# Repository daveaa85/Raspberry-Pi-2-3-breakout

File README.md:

This is an Eagle CAD project. It breaks out the 40 pin Raspberry Pi 2 and 3 io connector to a set of 3 rows of header pins.

It was created to make it easier to wire up and monitor pins. The way I use it is to populate the board with 2 rows of headers. The last set of holes are left open. That way DMM probes have a hole to drop into, and not slip off the target signal.

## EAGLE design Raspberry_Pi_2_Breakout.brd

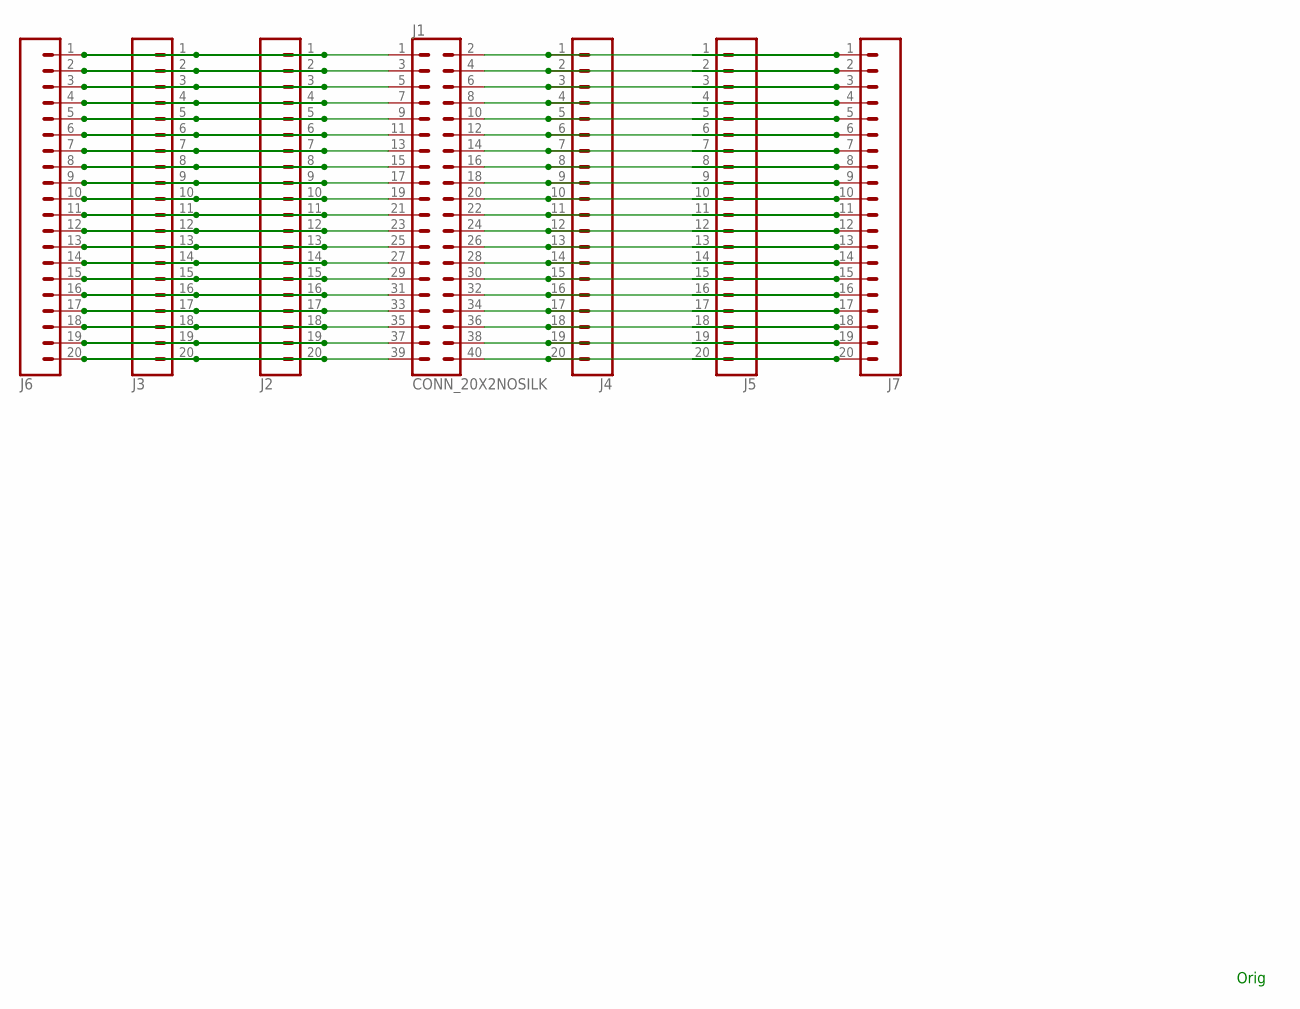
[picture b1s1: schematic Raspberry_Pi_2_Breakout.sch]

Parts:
J1: CONN_20X2NOSILK; 2X20_NOSILK
J2, J3, J4, J5, J6, J7: CONN_20NOSILK; 1X20_NOSILK

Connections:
unnamed: J1.1, J2.1, J3.1, J6.1
unnamed: J1.2, J4.1, J5.1, J7.1
unnamed: J1.4, J4.2, J5.2, J7.2
unnamed: J1.6, J4.3, J5.3, J7.3
unnamed: J1.8, J4.4, J5.4, J7.4
unnamed: J1.10, J4.5, J5.5, J7.5
unnamed: J1.12, J4.6, J5.6, J7.6
unnamed: J1.14, J4.7, J5.7, J7.7
unnamed: J1.16, J4.8, J5.8, J7.8
unnamed: J1.18, J4.9, J5.9, J7.9
unnamed: J1.20, J4.10, J5.10, J7.10
unnamed: J1.22, J4.11, J5.11, J7.11
unnamed: J1.24, J4.12, J5.12, J7.12
unnamed: J1.26, J4.13, J5.13, J7.13
unnamed: J1.28, J4.14, J5.14, J7.14
unnamed: J1.30, J4.15, J5.15, J7.15
unnamed: J1.32, J4.16, J5.16, J7.16
unnamed: J1.34, J4.17, J5.17, J7.17
unnamed: J1.36, J4.18, J5.18, J7.18
unnamed: J1.38, J4.19, J5.19, J7.19
unnamed: J1.40, J4.20, J5.20, J7.20
unnamed: J1.39, J2.20, J3.20, J6.20
unnamed: J1.37, J2.19, J3.19, J6.19
unnamed: J1.35, J2.18, J3.18, J6.18
unnamed: J1.33, J2.17, J3.17, J6.17
unnamed: J1.31, J2.16, J3.16, J6.16
unnamed: J1.29, J2.15, J3.15, J6.15
unnamed: J1.27, J2.14, J3.14, J6.14
unnamed: J1.25, J2.13, J3.13, J6.13
unnamed: J1.23, J2.12, J3.12, J6.12
unnamed: J1.21, J2.11, J3.11, J6.11
unnamed: J1.19, J2.10, J3.10, J6.10
unnamed: J1.17, J2.9, J3.9, J6.9
unnamed: J1.15, J2.8, J3.8, J6.8
unnamed: J1.13, J2.7, J3.7, J6.7
unnamed: J1.11, J2.6, J3.6, J6.6
unnamed: J1.9, J2.5, J3.5, J6.5
unnamed: J1.7, J2.4, J3.4, J6.4
unnamed: J1.5, J2.3, J3.3, J6.3
unnamed: J1.3, J2.2, J3.2, J6.2

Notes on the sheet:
Orig

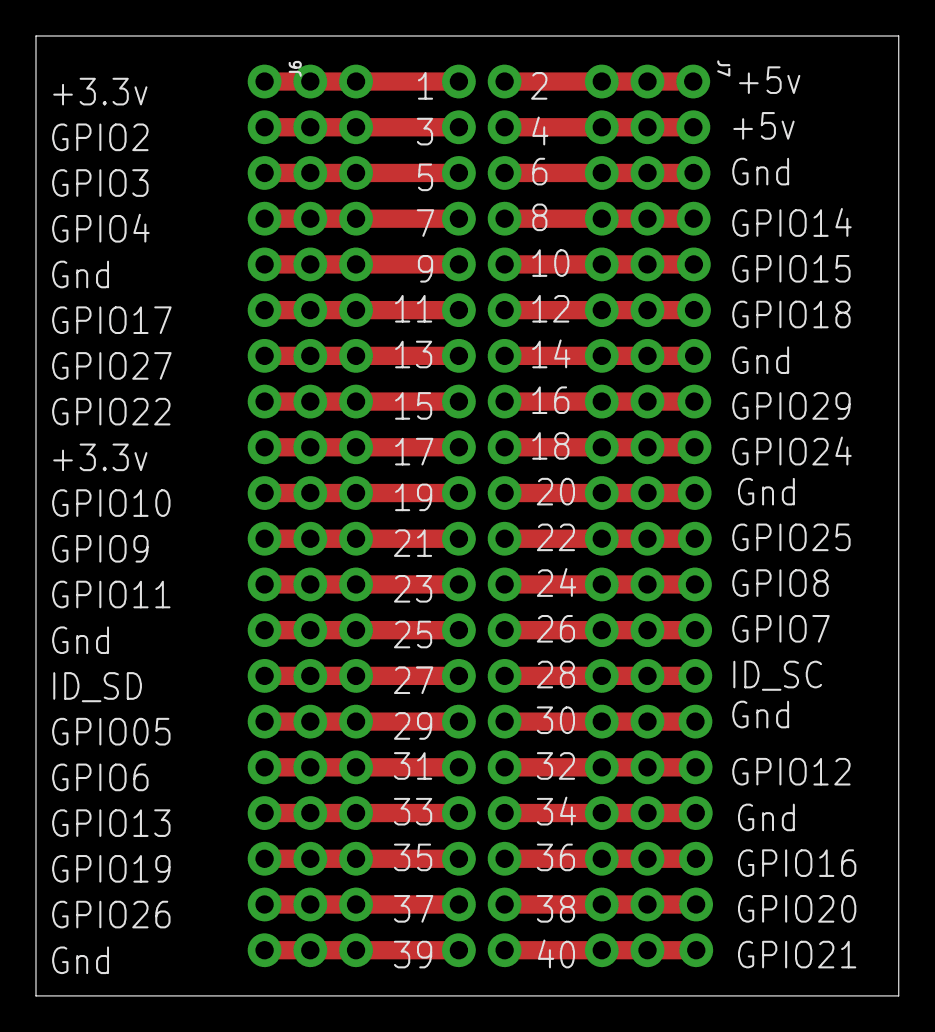
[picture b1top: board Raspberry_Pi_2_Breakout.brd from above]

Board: 2 copper layers, 47.9 x 53.3 mm, 7 parts (0 on the bottom side), 40 nets.

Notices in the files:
parts and their libraries:
SparkFun-Connectors: Licensing: Creative Commons ShareAlike 4.0 International - https://creativecommons.org/licenses/by-sa/4.0
